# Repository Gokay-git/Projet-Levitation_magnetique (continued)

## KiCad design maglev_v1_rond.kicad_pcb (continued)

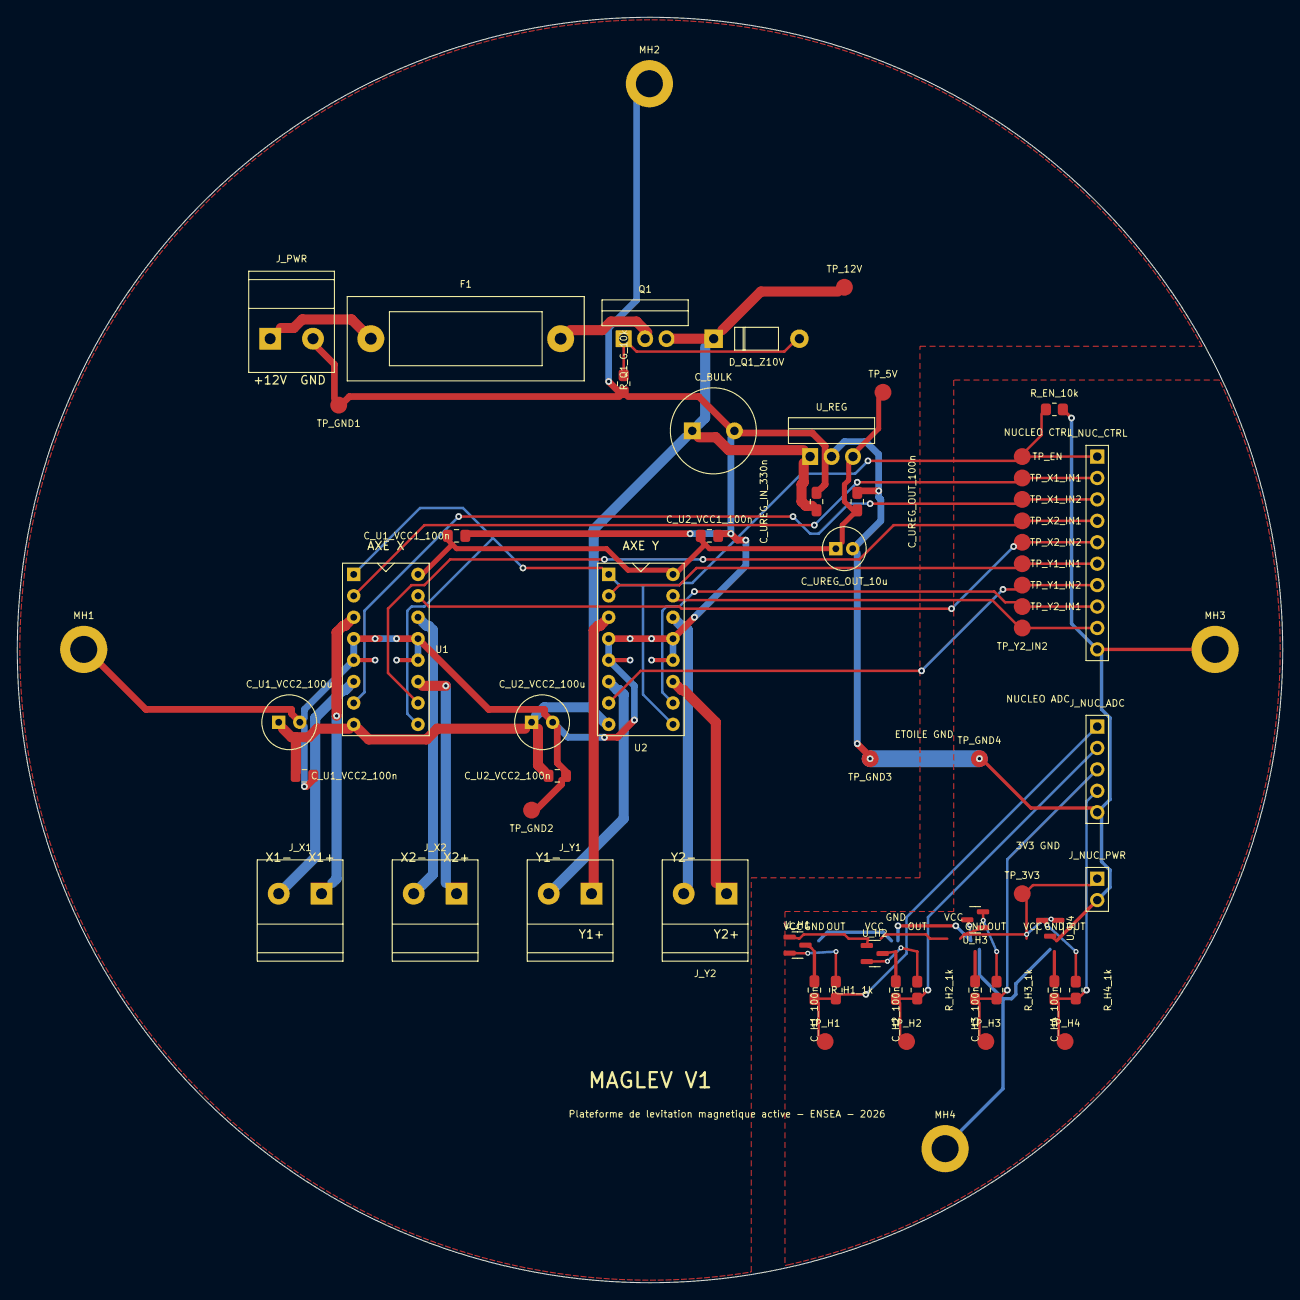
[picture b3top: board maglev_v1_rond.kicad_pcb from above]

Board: 2 copper layers, 150.0 x 150.0 mm, 62 parts (0 on the bottom side), 32 nets.

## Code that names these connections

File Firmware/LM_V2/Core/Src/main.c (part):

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    Error_Handler();
  }

  /** Configure Regular Channel : rang 1, I_X1 (PB0)
  */
  sConfig.Channel = ADC_CHANNEL_15;
  sConfig.Rank = ADC_REGULAR_RANK_1;
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    Error_Handler();
  }

  /** Configure Regular Channel : rang 2, I_X2 (PC1)
  */
  sConfig.Channel = ADC_CHANNEL_2;
  sConfig.Rank = ADC_REGULAR_RANK_2;
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    Error_Handler();
  }

  /** Configure Regular Channel : rang 3, I_Y1 (PC0)
  */
  sConfig.Channel = ADC_CHANNEL_1;
  sConfig.Rank = ADC_REGULAR_RANK_3;
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    Error_Handler();
  }

  /** Configure Regular Channel : rang 4, I_Y2 (PC2)
  */
  sConfig.Channel = ADC_CHANNEL_3;
  sConfig.Rank = ADC_REGULAR_RANK_4;
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    Error_Handler();
  }

  /** Configure Regular Channel : rang 5, HALL_1 (PA0)
  */
  sConfig.Channel = ADC_CHANNEL_5;
  sConfig.Rank = ADC_REGULAR_RANK_5;
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    Error_Handler();
  }

  /** Configure Regular Channel : rang 6, HALL_2 (PA1)
  */
  sConfig.Channel = ADC_CHANNEL_6;
  sConfig.Rank = ADC_REGULAR_RANK_6;
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    Error_Handler();
  }

  /** Configure Regular Channel : rang 7, HALL_3 (PA4)
  */
  sConfig.Channel = ADC_CHANNEL_9;
  sConfig.Rank = ADC_REGULAR_RANK_7;
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  __HAL_RCC_GPIOB_CLK_ENABLE();

  /*Configure GPIO pin Output Level */
  HAL_GPIO_WritePin(GPIOA, LD2_Pin|Y1_B_Pin|Y1_A_Pin, GPIO_PIN_RESET);

  /*Configure GPIO pin Output Level */
  HAL_GPIO_WritePin(GPIOB, X2_A_Pin|X2_B_Pin|X1_B_Pin|X1_A_Pin
                          |Y2_A_Pin|Y2_B_Pin, GPIO_PIN_RESET);

  /*Configure GPIO pin Output Level */
  HAL_GPIO_WritePin(TIMING_GPIO_Port, TIMING_Pin, GPIO_PIN_RESET);
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  GPIO_InitStruct.Pull = GPIO_NOPULL;
  HAL_GPIO_Init(B1_GPIO_Port, &GPIO_InitStruct);

  /*Configure GPIO pins : LD2_Pin Y1_B_Pin Y1_A_Pin */
  GPIO_InitStruct.Pin = LD2_Pin|Y1_B_Pin|Y1_A_Pin;
  GPIO_InitStruct.Mode = GPIO_MODE_OUTPUT_PP;
  GPIO_InitStruct.Pull = GPIO_NOPULL;
  GPIO_InitStruct.Speed = GPIO_SPEED_FREQ_LOW;
  HAL_GPIO_Init(GPIOA, &GPIO_InitStruct);

  /*Configure GPIO pins : X2_A_Pin X2_B_Pin X1_B_Pin X1_A_Pin
                           Y2_A_Pin Y2_B_Pin */
  GPIO_InitStruct.Pin = X2_A_Pin|X2_B_Pin|X1_B_Pin|X1_A_Pin
                          |Y2_A_Pin|Y2_B_Pin;
  GPIO_InitStruct.Mode = GPIO_MODE_OUTPUT_PP;
  GPIO_InitStruct.Pull = GPIO_NOPULL;
  GPIO_InitStruct.Speed = GPIO_SPEED_FREQ_LOW;
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
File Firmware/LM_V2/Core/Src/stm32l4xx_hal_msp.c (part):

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    __HAL_RCC_GPIOA_CLK_ENABLE();
    __HAL_RCC_GPIOB_CLK_ENABLE();
    /**ADC1 GPIO Configuration
    PC0     ------> ADC1_IN1   (I_Y1)
    PC1     ------> ADC1_IN2   (I_X2)
    PC2     ------> ADC1_IN3   (I_Y2)
    PC3     ------> ADC1_IN4   (VBUS)
    PA0     ------> ADC1_IN5   (HALL_1)
    PA1     ------> ADC1_IN6   (HALL_2)
    PA4     ------> ADC1_IN9   (HALL_3)
    PB0     ------> ADC1_IN15  (I_X1)
    */
    GPIO_InitStruct.Pin = GPIO_PIN_0|GPIO_PIN_1|GPIO_PIN_2|GPIO_PIN_3;
    GPIO_InitStruct.Mode = GPIO_MODE_ANALOG_ADC_CONTROL;
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    /* USER CODE END TIM1_MspPostInit 0 */
    __HAL_RCC_GPIOA_CLK_ENABLE();
    /**TIM1 GPIO Configuration
    PA8     ------> TIM1_CH1   (EN_X1)
    PA9     ------> TIM1_CH2   (EN_X2)
    PA10     ------> TIM1_CH3  (EN_Y1)
    PA11     ------> TIM1_CH4  (EN_Y2)
    */
    GPIO_InitStruct.Pin = GPIO_PIN_8|GPIO_PIN_9|GPIO_PIN_10|GPIO_PIN_11;
    GPIO_InitStruct.Mode = GPIO_MODE_AF_PP;
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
